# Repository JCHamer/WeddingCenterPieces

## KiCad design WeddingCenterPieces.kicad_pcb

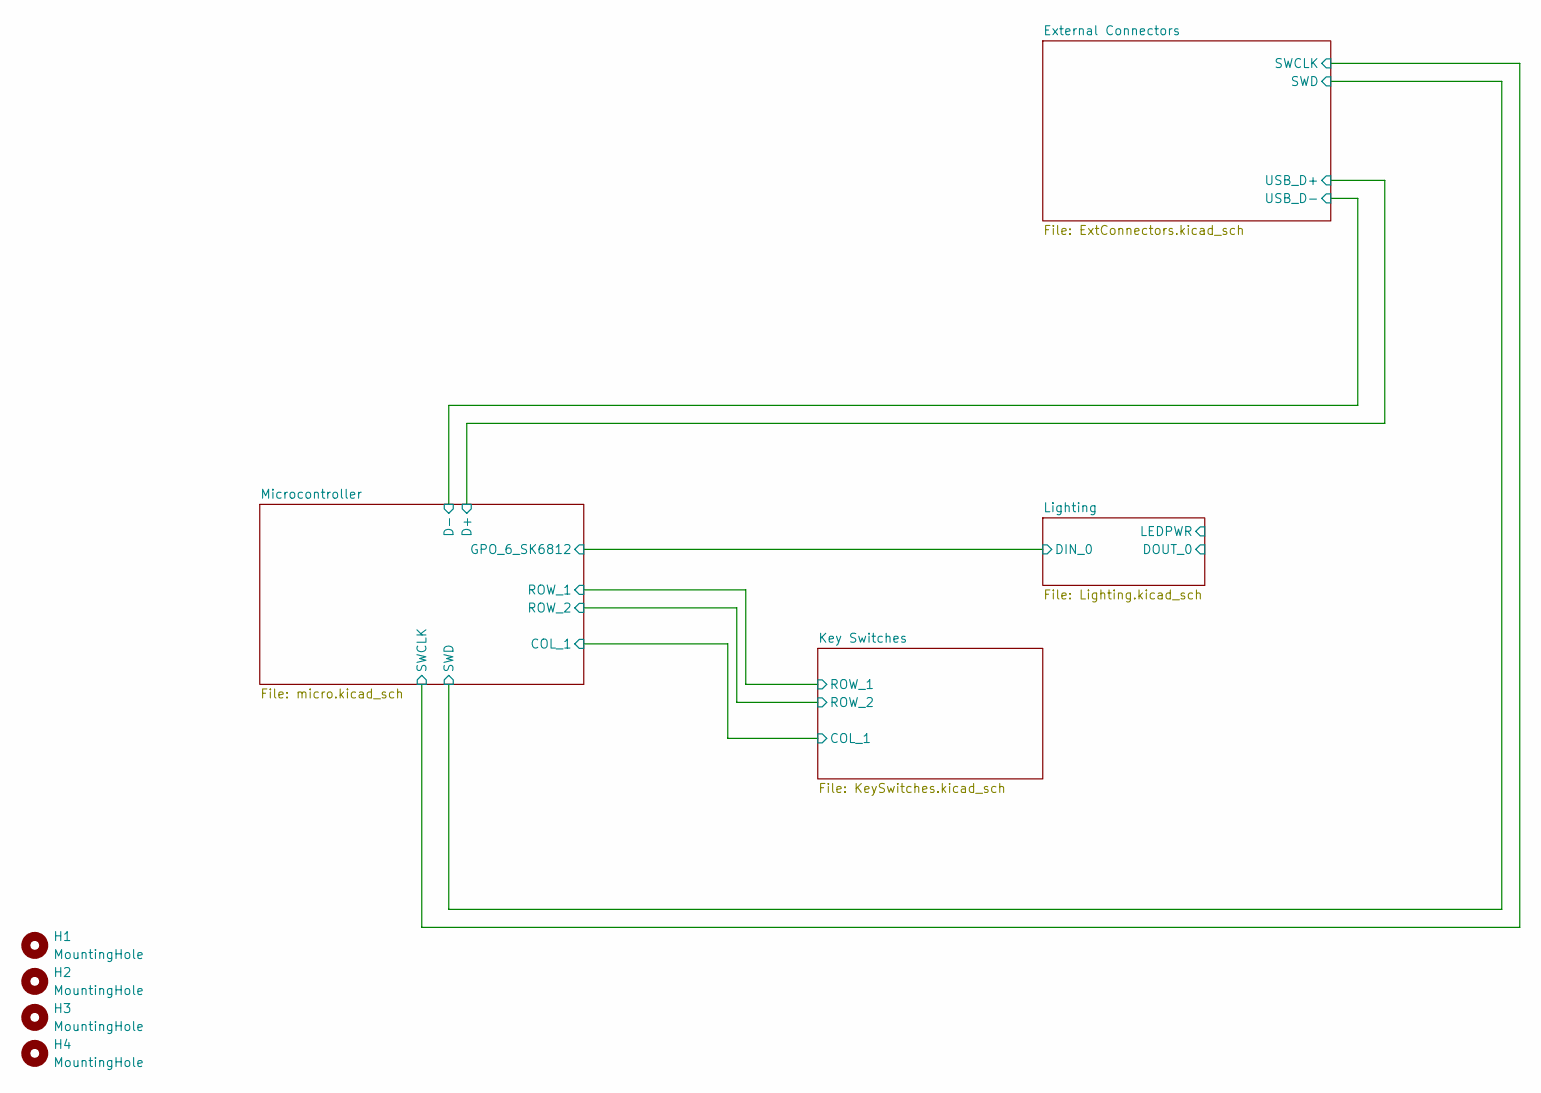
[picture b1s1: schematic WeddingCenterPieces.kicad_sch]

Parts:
H1, H2, H3, H4: MountingHole; MountingHole_2.7mm_M2.5

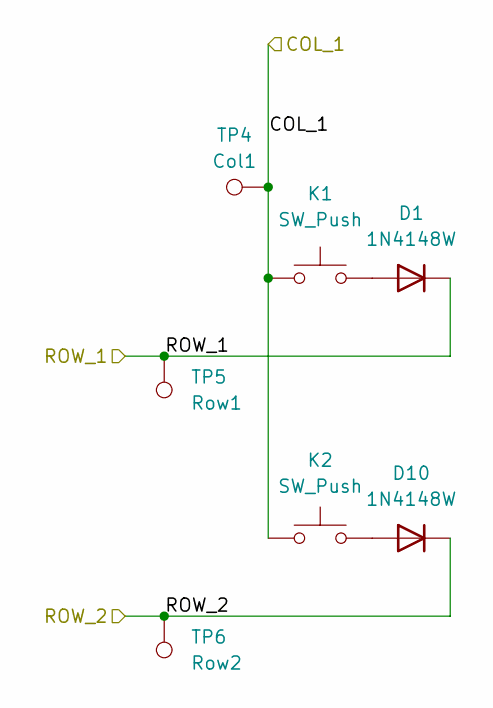
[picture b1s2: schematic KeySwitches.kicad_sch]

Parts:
D1, D10: 1N4148W; D_SOD-123
K1: SW_Push; Kailh_socket_MX_optional_reversible
K2: SW_Push; Kailh_socket_MX
TP4: Col1; TestPoint_Pad_D1.5mm
TP5: Row1; TestPoint_Pad_D1.5mm
TP6: Row2; TestPoint_Pad_D1.5mm

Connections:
/Key Switches/COL_1: K1.1, K2.1, TP4.1; also elsewhere on the board
/Key Switches/ROW_1: D1.1 (K), TP5.1; also elsewhere on the board
/Key Switches/ROW_2: D10.1 (K), TP6.1; also elsewhere on the board
unnamed: D1.2 (A), K1.2
unnamed: D10.2 (A), K2.2

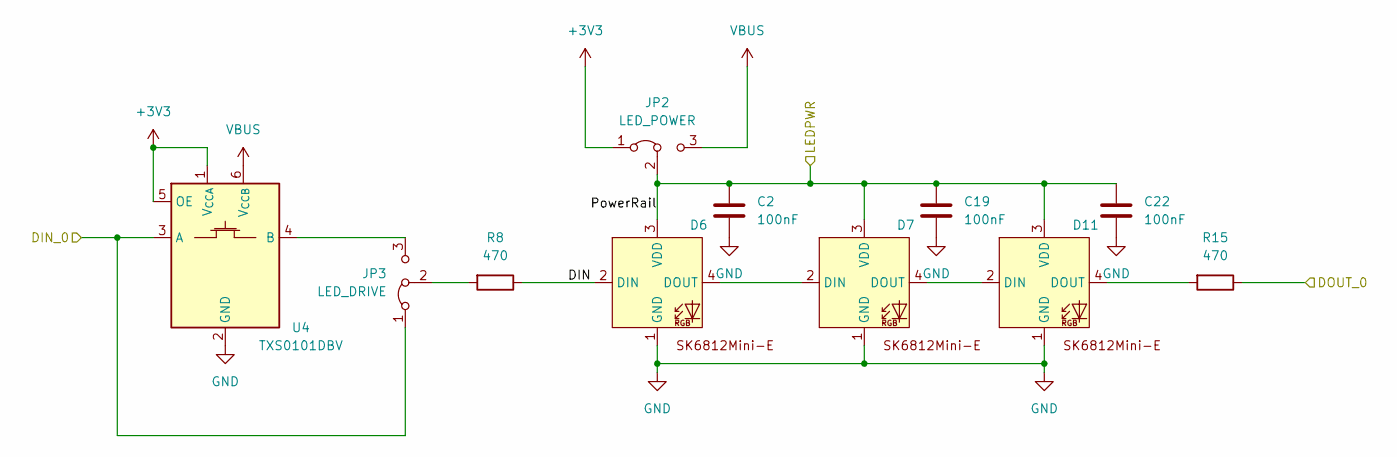
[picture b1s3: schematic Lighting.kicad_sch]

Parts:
C2, C19, C22: 100nF; C_0805_2012Metric_Pad1.18x1.45mm_HandSolder
D6, D7, D11: SK6812-MINI-E_ReverseMount
JP2: LED_POWER; PinHeader_1x03_P2.54mm_Vertical
JP3: LED_DRIVE; PinHeader_1x03_P2.54mm_Vertical
R8, R15: 470; R_0805_2012Metric_Pad1.20x1.40mm_HandSolder
U4: TXS0101DBV; SOT-23-6

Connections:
+3V3: JP2.1 (A), U4.1 (V_{CCA}), U4.5 (OE); also elsewhere on the board
/External Connectors/LED_Data: R15.1
/Lighting/DIN: D6.2 (DIN), R8.1
/Lighting/DIN_0: JP3.1 (A), U4.3 (A); also elsewhere on the board
/Lighting/PowerRail: C2.1, C19.1, C22.1, D6.3 (VDD), D7.3 (VDD), D11.3 (VDD), JP2.2 (C)
GND: C2.2, C19.2, C22.2, D6.1 (GND), D7.1 (GND), D11.1 (GND), U4.2 (GND); also elsewhere on the board
unnamed: D6.4 (DOUT), D7.2 (DIN)
unnamed: D7.4 (DOUT), D11.2 (DIN)
unnamed: D11.4 (DOUT), R15.2
unnamed: JP3.3 (B), U4.4 (B)
unnamed: JP3.2 (C), R8.2
VBUS: JP2.3 (B), U4.6 (V_{CCB}); also elsewhere on the board

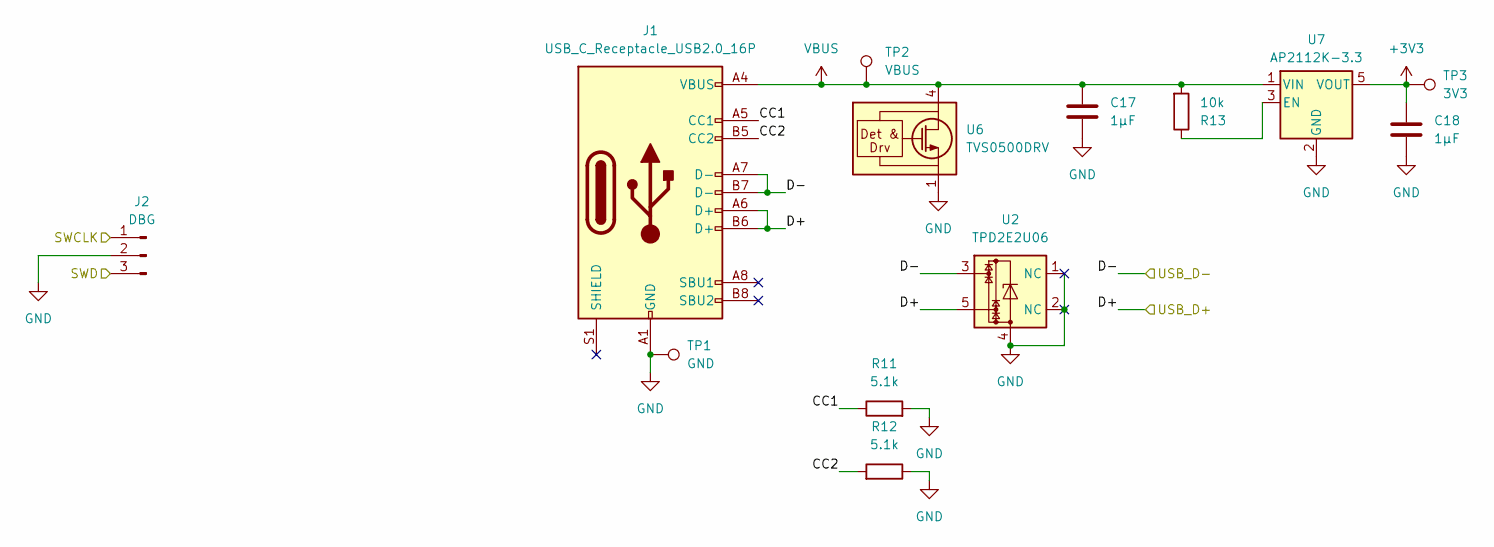
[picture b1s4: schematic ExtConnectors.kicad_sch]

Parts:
C17, C18: 1μF; C_0805_2012Metric_Pad1.18x1.45mm_HandSolder
J1: USB_C_Receptacle_USB2.0_16P; USB_C_Receptacle_GCT_USB4105-xx-A_16P_TopMnt_Horizontal
J2: DBG; PinHeader_1x03_P2.54mm_Vertical
R11, R12: 5.1k; R_0805_2012Metric_Pad1.20x1.40mm_HandSolder
R13: 10k; R_0805_2012Metric_Pad1.20x1.40mm_HandSolder
TP1: GND; TestPoint_Pad_1.5x1.5mm
TP2: VBUS; TestPoint_Pad_D1.5mm
TP3: 3V3; TestPoint_Pad_D1.5mm
U2: TPD2E2U06; SOT-553
U6: TVS0500DRV; WSON-6-1EP_2x2mm_P0.65mm_EP1x1.6mm
U7: AP2112K-3.3; SOT-23-5

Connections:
+3V3: C18.1, TP3.1, U7.5 (VOUT); also elsewhere on the board
/External Connectors/CC1: J1.A5 (CC1), R11.1
/External Connectors/CC2: J1.B5 (CC2), R12.2
/External Connectors/D+: J1.A6 (D+), J1.B6 (D+), U2.5; also elsewhere on the board
/External Connectors/D-: J1.A7 (D-), J1.B7 (D-), U2.3; also elsewhere on the board
/External Connectors/SWCLK: J2.1; also elsewhere on the board
/External Connectors/SWD: J2.3; also elsewhere on the board
GND: C17.2, C18.2, J1.A1 (GND), J1.A12 (GND), J1.B1 (GND), J1.B12 (GND), J2.2, R11.2, R12.1, TP1.1, U2.1 (NC), U2.2 (NC), U2.4, U6.1 (GND), U6.2 (GND), U6.3 (GND), U6.7 (GND), U7.2 (GND); also elsewhere on the board
unnamed: R13.1, U7.3 (EN)
VBUS: C17.1, J1.A4 (VBUS), J1.A9 (VBUS), J1.B4 (VBUS), J1.B9 (VBUS), R13.2, TP2.1, U6.4 (IN), U6.5 (IN), U6.6 (IN), U7.1 (VIN); also elsewhere on the board

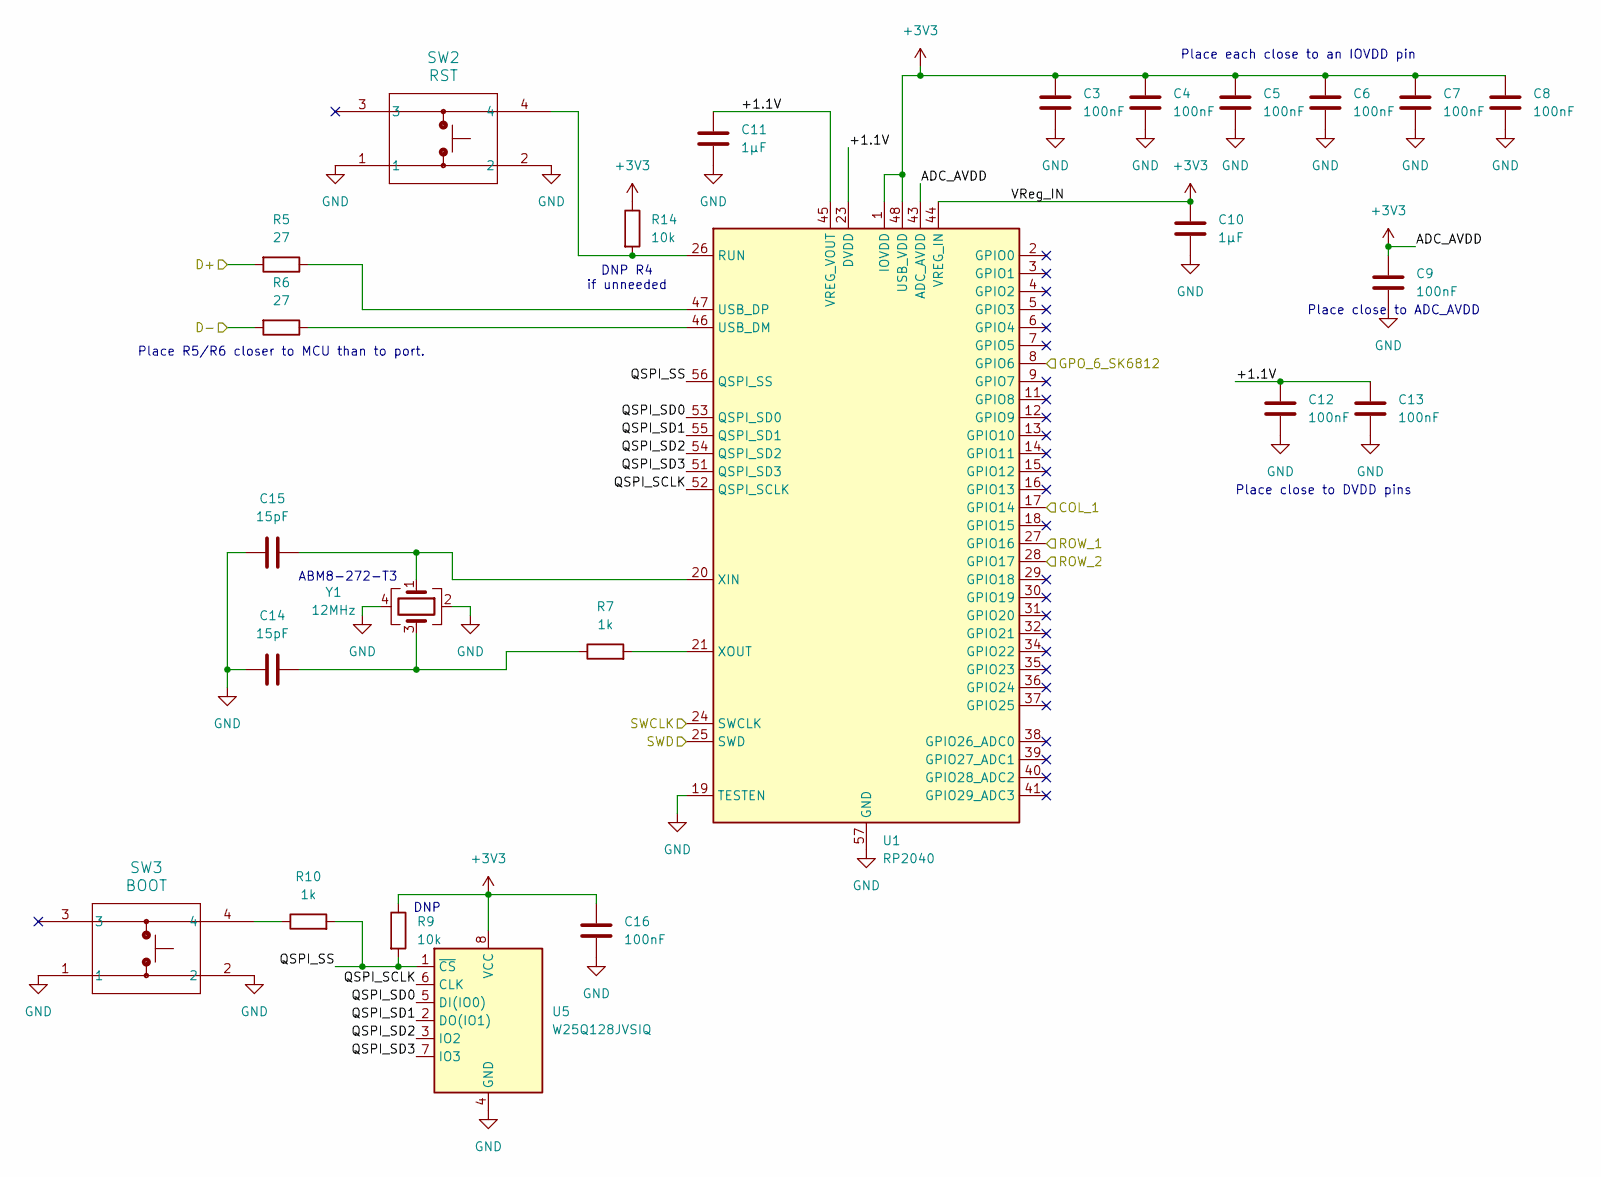
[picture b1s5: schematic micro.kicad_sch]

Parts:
C3, C4, C5, C6, C7, C8, C9, C12, C13: 100nF; C_0603_1608Metric_Pad1.08x0.95mm_HandSolder
C10, C11: 1μF; C_0603_1608Metric_Pad1.08x0.95mm_HandSolder
C14, C15: 15pF; C_0603_1608Metric_Pad1.08x0.95mm_HandSolder
C16: 100nF; C_0805_2012Metric_Pad1.18x1.45mm_HandSolder
R5, R6: 27; R_0603_1608Metric_Pad0.98x0.95mm_HandSolder
R7: 1k; R_0603_1608Metric_Pad0.98x0.95mm_HandSolder
R9, R14: 10k; R_0805_2012Metric_Pad1.20x1.40mm_HandSolder
R10: 1k; R_0805_2012Metric_Pad1.20x1.40mm_HandSolder
SW2: RST; TL3342_EWI
SW3: BOOT; TL3342_EWI
U1: RP2040; QFN-56-1EP_7x7mm_P0.4mm_EP3.2x3.2mm
U5: W25Q128JVSIQ; SOIC-8_5.23x5.23mm_P1.27mm
Y1: 12MHz; ABM8272T3

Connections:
+3V3: C3.1, C4.1, C5.1, C6.1, C7.1, C8.1, C9.1, C10.1, C16.1, R9.1, R14.1, U1.1 (IOVDD), U1.10 (IOVDD), U1.22 (IOVDD), U1.33 (IOVDD), U1.42 (IOVDD), U1.43 (ADC_AVDD), U1.44 (VREG_IN), U1.48 (USB_VDD), U1.49 (IOVDD), U5.8 (VCC); also elsewhere on the board
/9VTo5VSupply/VBatt_Sense: U1.40 (GPIO28_ADC2)
/External Connectors/Btn-: U1.11 (GPIO8)
/External Connectors/D+: R5.2; also elsewhere on the board
/External Connectors/D-: R6.2; also elsewhere on the board
/External Connectors/SWCLK: U1.24 (SWCLK); also elsewhere on the board
/External Connectors/SWD: U1.25 (SWD); also elsewhere on the board
/Key Switches/COL_1: U1.17 (GPIO14); also elsewhere on the board
/Key Switches/ROW_1: U1.27 (GPIO16); also elsewhere on the board
/Key Switches/ROW_2: U1.28 (GPIO17); also elsewhere on the board
/Lighting/DIN_0: U1.8 (GPIO6); also elsewhere on the board
/Microcontroller/+1.1V: C11.1, C12.1, C13.1, U1.23 (DVDD), U1.45 (VREG_VOUT), U1.50 (DVDD)
/Microcontroller/QSPI_SCLK: U1.52 (QSPI_SCLK), U5.6 (CLK)
/Microcontroller/QSPI_SD0: U1.53 (QSPI_SD0), U5.5 (DI(IO0))
/Microcontroller/QSPI_SD1: U1.55 (QSPI_SD1), U5.2 (DO(IO1))
/Microcontroller/QSPI_SD2: U1.54 (QSPI_SD2), U5.3 (IO2)
/Microcontroller/QSPI_SD3: U1.51 (QSPI_SD3), U5.7 (IO3)
/Microcontroller/QSPI_SS: R9.2, R10.2, U1.56 (QSPI_SS), U5.1 (~CS)
GND: C3.2, C4.2, C5.2, C6.2, C7.2, C8.2, C9.2, C10.2, C11.2, C12.2, C13.2, C14.1, C15.1, C16.2, SW2.1, SW2.2, SW3.1, SW3.2, U1.19 (TESTEN), U1.57 (GND), U5.4 (GND), Y1.2, Y1.4; also elsewhere on the board
unnamed: C14.2, R7.1, Y1.3
unnamed: R10.1, SW3.4
unnamed: R14.2, SW2.4, U1.26 (RUN)
unnamed: R6.1, U1.46 (USB_DM)
unnamed: R5.1, U1.47 (USB_DP)
unnamed: C15.2, U1.20 (XIN), Y1.1
unnamed: R7.2, U1.21 (XOUT)

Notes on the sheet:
Place R5/R6 closer to MCU than to port.
Place close to ADC_AVDD
DNP R4 if unneeded
ABM8-272-T3
DNP
Place each close to an IOVDD pin
Place close to DVDD pins

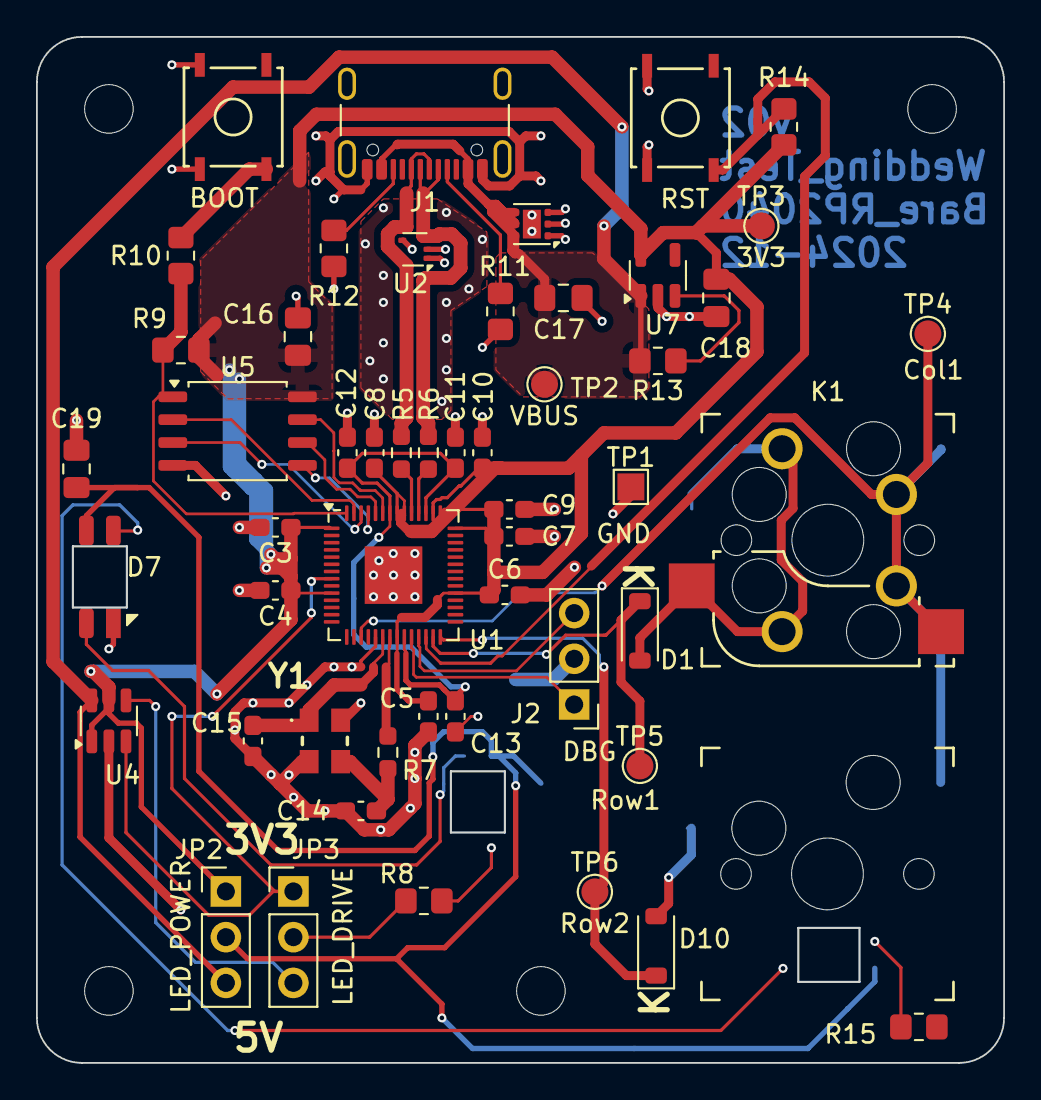
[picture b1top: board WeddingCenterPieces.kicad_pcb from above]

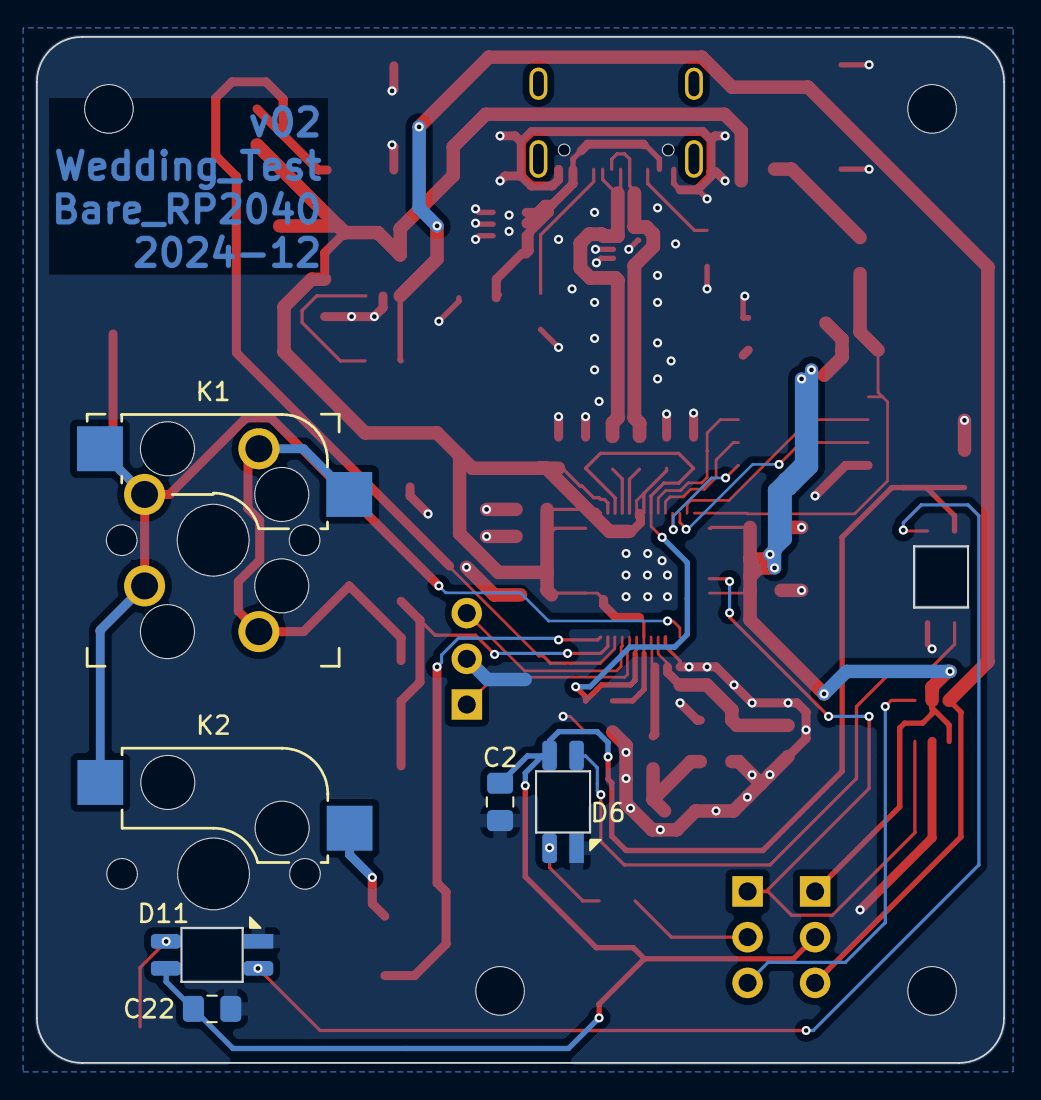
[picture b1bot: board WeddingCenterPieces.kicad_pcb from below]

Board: 2 copper layers, 53.7 x 57.0 mm, 60 parts (5 on the bottom side), 37 nets.

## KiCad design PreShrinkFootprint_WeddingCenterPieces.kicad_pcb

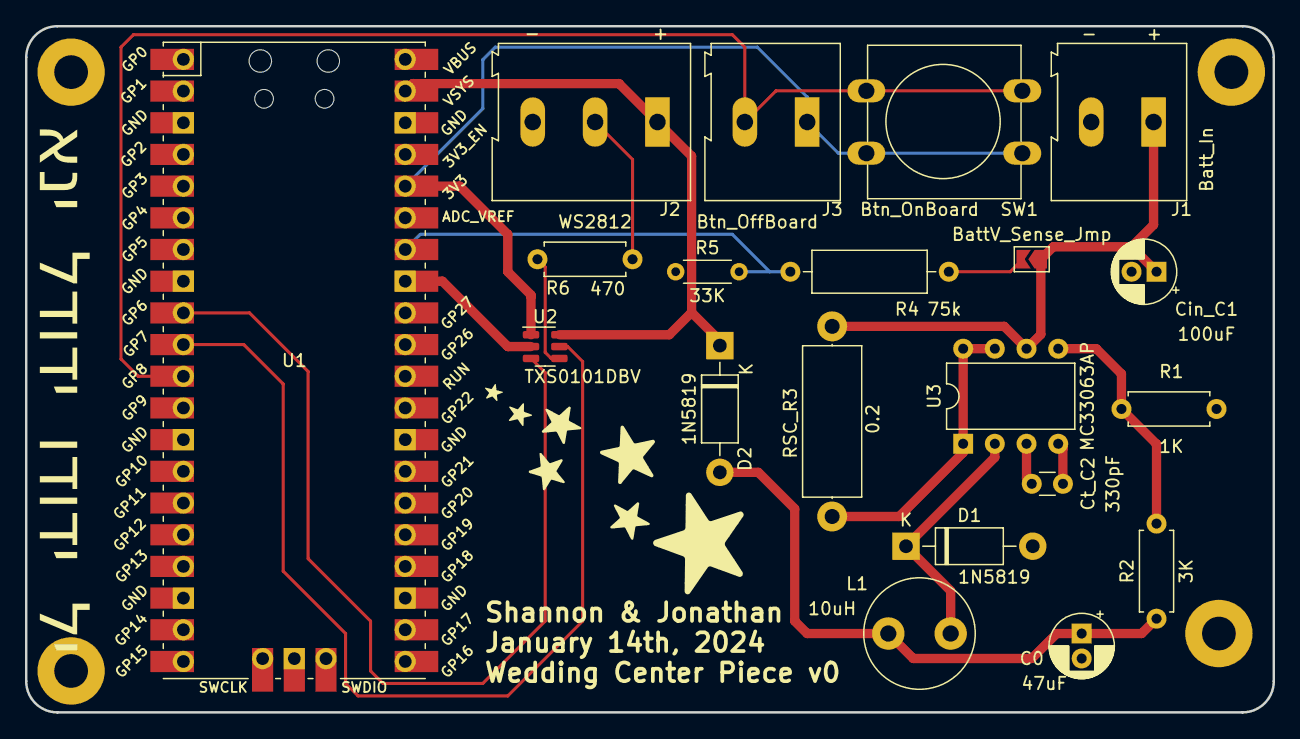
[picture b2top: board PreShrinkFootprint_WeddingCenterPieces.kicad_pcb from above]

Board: 2 copper layers, 100.0 x 55.0 mm, 24 parts (0 on the bottom side), 16 nets.

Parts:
C0: 47uF; CP_Radial_D5.0mm_P2.00mm
Cin_C1: 100uF; CP_Radial_D5.0mm_P2.00mm
Ct_C2: 330pF; C_Disc_D3.0mm_W1.6mm_P2.50mm
D1, D2: 1N5819; D_DO-41_SOD81_P10.16mm_Horizontal
H1, H2, H3, H4: MountingHole_Pad; MountingHole_2.7mm_M2.5_Pad
J1: Batt_In; TerminalBlock_Altech_AK300-2_P5.00mm
J2: WS2812; TerminalBlock_Altech_AK300-3_P5.00mm
J3: Btn_OffBoard; TerminalBlock_Altech_AK300-2_P5.00mm
JP1: BattV_Sense_Jmp; SolderJumper-2_P1.3mm_Open_TrianglePad1.0x1.5mm
L1: 10uH; L_Radial_D8.7mm_P5.00mm_Fastron_07HCP
R1: 1K; R_Axial_DIN0207_L6.3mm_D2.5mm_P7.62mm_Horizontal
R2: 3K; R_Axial_DIN0207_L6.3mm_D2.5mm_P7.62mm_Horizontal
R4: 75k; R_Axial_DIN0309_L9.0mm_D3.2mm_P12.70mm_Horizontal
R5: 33K; R_Axial_DIN0204_L3.6mm_D1.6mm_P5.08mm_Horizontal
R6: 470; R_Axial_DIN0207_L6.3mm_D2.5mm_P7.62mm_Horizontal
RSC_R3: 0.2; R_Axial_DIN0414_L11.9mm_D4.5mm_P15.24mm_Horizontal
SW1: Btn_OnBoard; SW_PUSH-12mm
U1: Pico; RPi_Pico_SMD_TH
U2: TXS0101DBV; SOT-23-6
U3: MC33063AP; DIP-8_W7.62mm

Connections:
+3V3: J3.1, SW1.1 (A), U1.36 (3V3), U2.1 (V_{CCA})
+5V: D2.1 (K), J2.1, U1.39 (VSYS), U2.6 (V_{CCB})
/Batt+: Cin_C1.1, J1.1, JP1.1 (A), RSC_R3.1, U3.6 (Vin)
/Data_5V: J2.2, R6.2
GND: C0.2, Cin_C1.2, Ct_C2.2, D1.2 (A), H1.1, H2.1, H3.1, H4.1, J1.2, J2.3, R1.2, R5.1, U1.3 (GND), U1.8 (GND), U1.13 (GND), U1.18 (GND), U1.23 (GND), U1.28 (GND), U1.33 (AGND), U1.38 (GND), U2.2 (GND), U3.4 (GND)
unnamed: D1.1 (K), L1.1, U3.2 (SwE)
unnamed: C0.1, D2.2 (A), L1.2, R2.1
unnamed: J3.2, SW1.2 (B), U1.11 (GPIO8)
unnamed: JP1.2 (B), R4.2
unnamed: U1.9 (GPIO6), U2.3 (A)
unnamed: U1.10 (GPIO7), U2.5 (OE)
unnamed: R4.1, R5.2, U1.34 (GPIO28_ADC2)
unnamed: R6.1, U2.4 (B)
unnamed: RSC_R3.2, U3.1 (SwC), U3.7 (Ipk), U3.8 (DC)
unnamed: Ct_C2.1, U3.3 (TC)
unnamed: R1.1, R2.2, U3.5 (Vfb)

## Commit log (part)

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2023-12-02 Initial Commit. A little late. Schematic and PCB v0 completed, ordered, assembled, and functioning.
2023-12-02 Updated PCB to v1 for bulk order
    Moved a trace on the bottom layer to the edge to avoid splitting the ground plane, it travels on the upper layer to get to and from the edge and then jumps to the bottom layer to cross the lines in t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
    Additionally, vertical bars have been added next to all pins that need to be connected on the surface mount pads in order to mount the RaspberryPi Pico with its castellated edges as a surface mount c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
2023-12-02 Removed stale pcb alt
    Removed the larger footprint alternate PCB (first version of the PCB before shrinking to a smaller space) as the newer smaller layout has been permanently selected.
2024-12-01 Pulling out Power Supply into a separate sheet.
2024-12-15 WIP: Updating board to use an RP2040 directly.
    TODO: Need to update on-board LEDs to SK6812 Mini-E, fix VSYS/VBUS/+5V, and convert any footprints of interest to SMD
2024-12-21 WIP: Updated SK6812Mini to SK6812Mini-E and remapped ref des keys between PCB and Schematic.
2024-12-27 Placing nearly all components onto the PCB. Removing the 9Vto5V battery input stage from populating onto the PCB.
2024-12-27 Added testpoints, finished placing components, fixed footprint mapping, and ready to start routing tracks.
2024-12-27 Updating SK6812 circuit to match suggested application from datasheet, adding a resistor at the last DOut and filter caps to each LED.
2024-12-28 Adding additional LEDs and driver to test per-key LEDs, updating net classes and design constraints, and starting to route tracks.
2024-12-30 Shrinking board to only have 2 key switches and a few other unnecessary components. Finished with routing the rest of the board.
2024-12-30 Outputs generated and prepared for ordering.
